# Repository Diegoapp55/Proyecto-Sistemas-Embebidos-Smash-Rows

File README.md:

# Proyecto-Sistemas-Embebidos
Repositorio para el proyecto de Sistemas Embebidos 2022-2: Smash Rows

En la wiki de este repositorio se encuentra la documentación al respecto del proyecto.

Integrantes: 
* Raúl Andrés Guzmán Mayorga
* Sergio Andrés Guevara Contreras
* Diego Alejandro Sánchez Mendoza
* Eduardo Toro Bernal

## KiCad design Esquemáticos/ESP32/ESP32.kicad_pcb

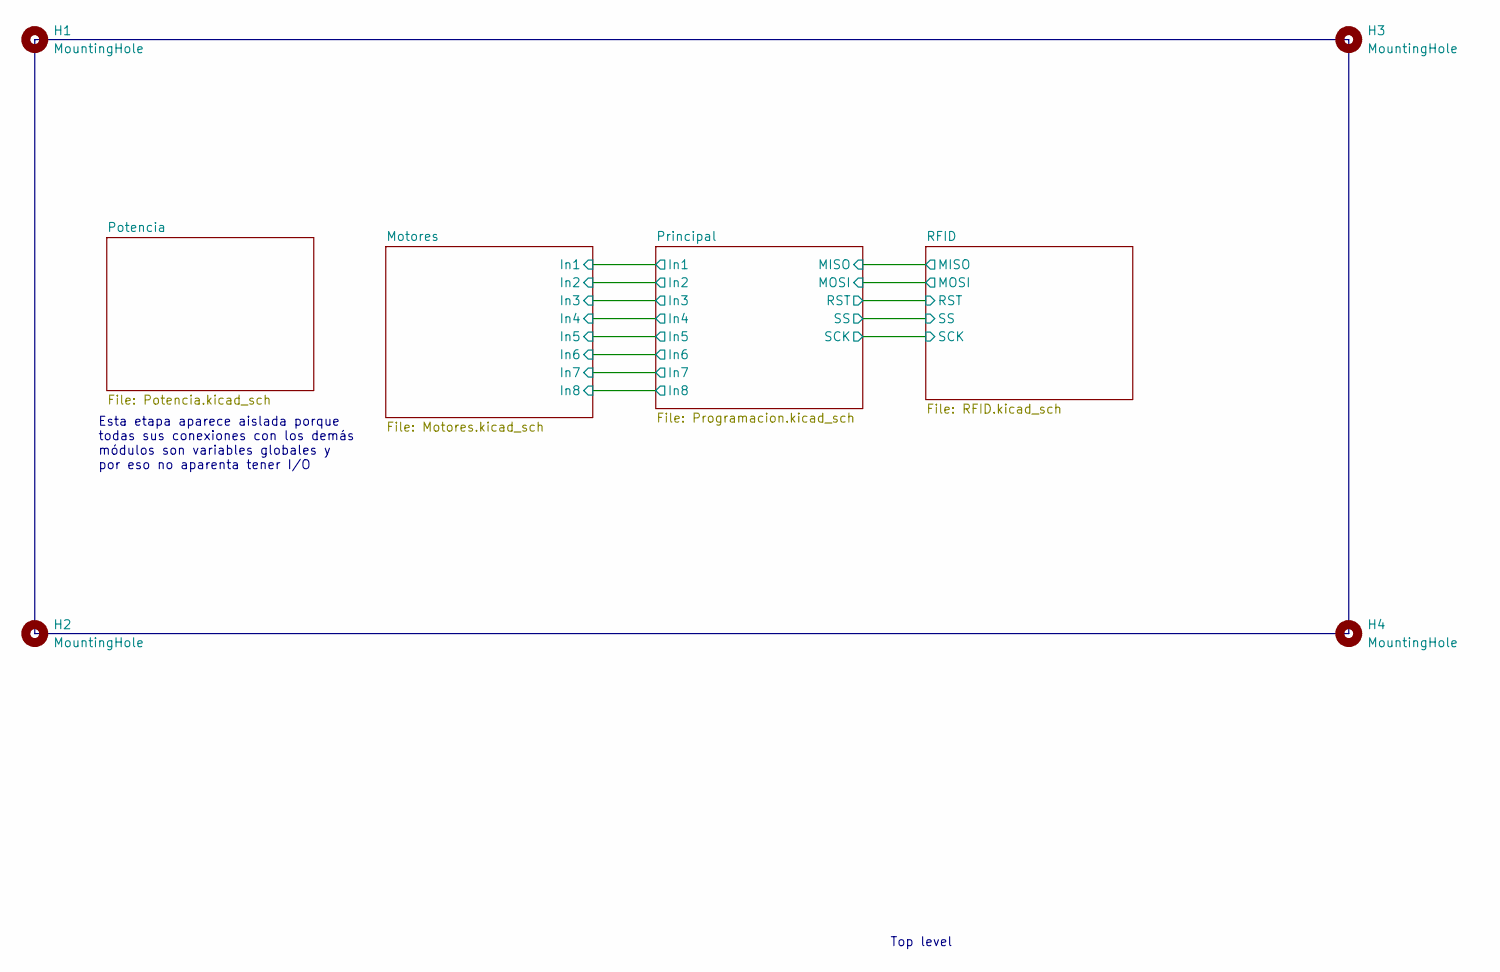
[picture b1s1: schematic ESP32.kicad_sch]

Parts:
H1, H2, H3, H4: MountingHole; MountingHole_2.5mm

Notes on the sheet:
Esta etapa aparece aislada porque todas sus conexiones con los demás módulos son variables globales y por eso no aparenta tener I/O
Top level

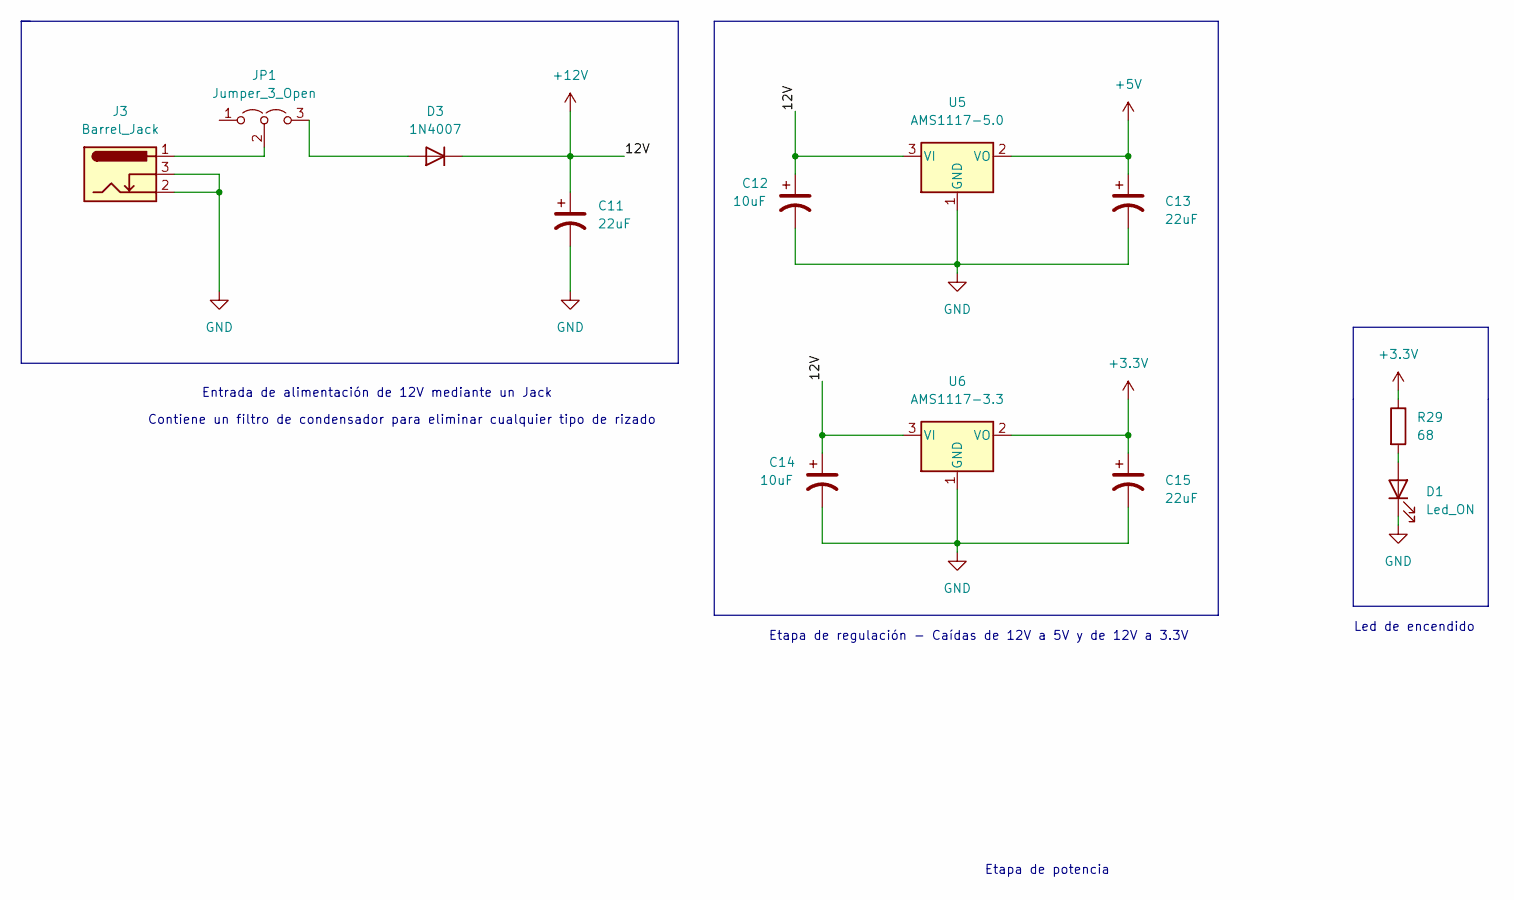
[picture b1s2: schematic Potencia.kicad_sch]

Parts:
C11, C13, C15: 22uF; C_0805_2012Metric_Pad1.18x1.45mm_HandSolder
C12, C14: 10uF; C_0805_2012Metric_Pad1.18x1.45mm_HandSolder
D1: Led_ON; LED_0603_1608Metric_Pad1.05x0.95mm_HandSolder
D3: 1N4007; D_SMA_Handsoldering
J3: Barrel_Jack; BarrelJack_GCT_DCJ200-10-A_Horizontal
JP1: Jumper_3_Open; PinHeader_1x03_P2.54mm_Vertical
R29: 68; R_1206_3216Metric_Pad1.30x1.75mm_HandSolder
U5: AMS1117-5.0; SOT-223-3_TabPin2
U6: AMS1117-3.3; SOT-223-3_TabPin2

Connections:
+3.3V: C15.1, R29.1, U6.2 (VO); also elsewhere on the board
+12V: C11.1, C12.1, C14.1, D3.1 (K), U5.3 (VI), U6.3 (VI)
GND: C11.2, C12.2, C13.2, C14.2, C15.2, D1.1 (K), J3.2, J3.3, U5.1 (GND), U6.1 (GND); also elsewhere on the board
unnamed: D1.2 (A), R29.2
unnamed: D3.2 (A), JP1.3 (B)
unnamed: J3.1, JP1.2 (C)

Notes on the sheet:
Entrada de alimentación de 12V mediante un Jack
Led de encendido
Contiene un filtro de condensador para eliminar cualquier tipo de rizado
Etapa de regulación - Caídas de 12V a 5V y de 12V a 3.3V
Etapa de potencia

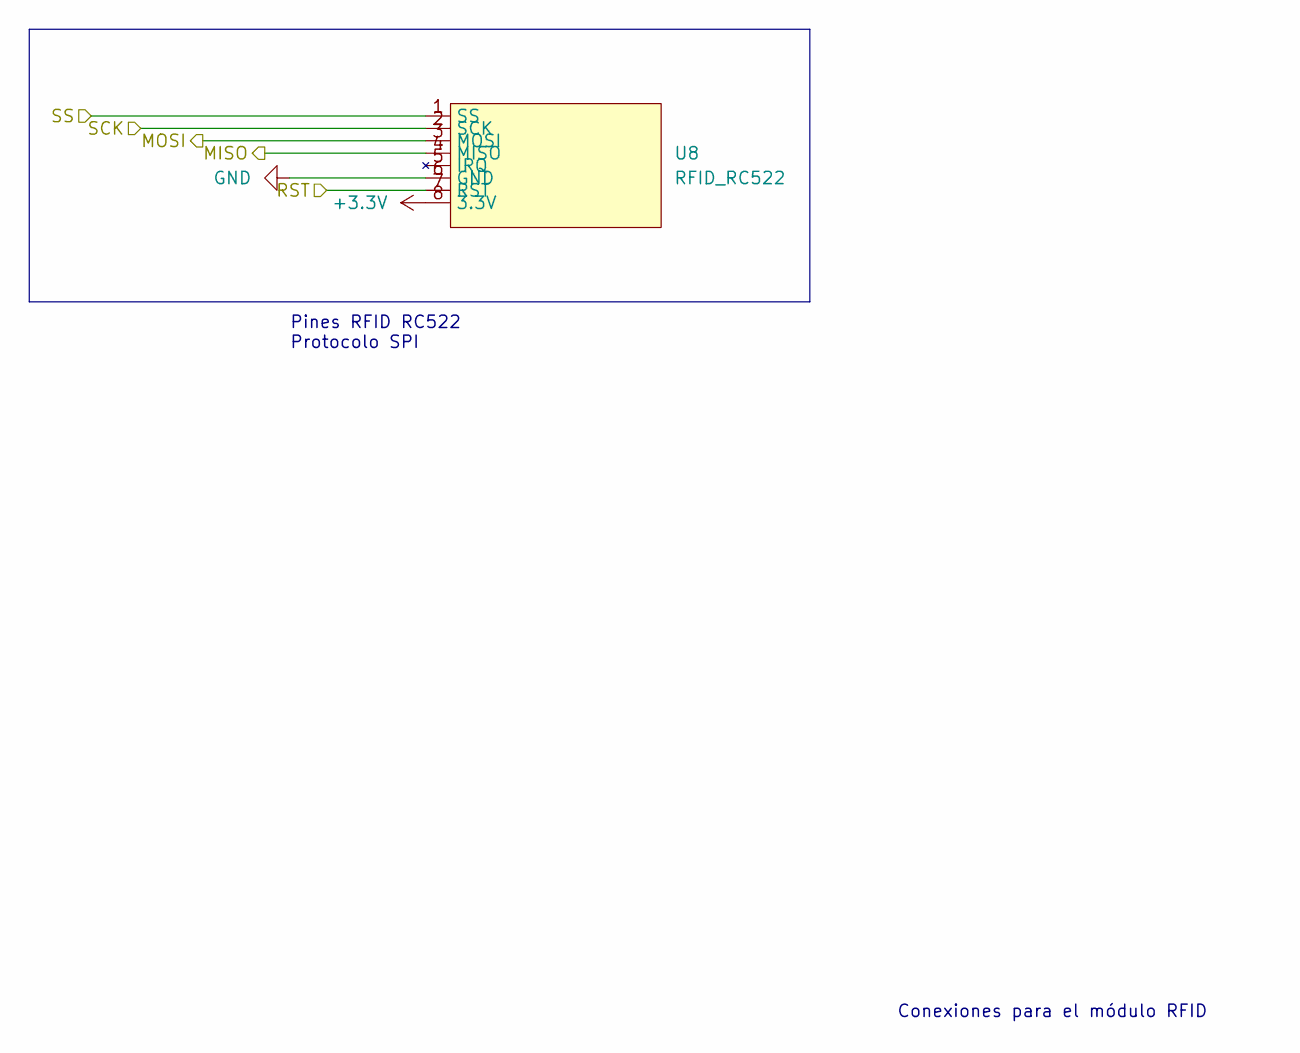
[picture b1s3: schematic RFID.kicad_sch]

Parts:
U8: RFID_RC522; JST_EH_B8B-EH-A_1x08_P2.50mm_Vertical

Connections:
+3.3V: U8.8 (3.3V); also elsewhere on the board
/Principal/MISO: U8.4 (MISO); also elsewhere on the board
/Principal/MOSI: U8.3 (MOSI); also elsewhere on the board
/Principal/RST: U8.7 (RST); also elsewhere on the board
/Principal/SCK: U8.2 (SCK); also elsewhere on the board
/Principal/SS: U8.1 (SS); also elsewhere on the board
GND: U8.6 (GND); also elsewhere on the board

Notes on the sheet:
Conexiones para el módulo RFID
Pines RFID RC522 Protocolo SPI

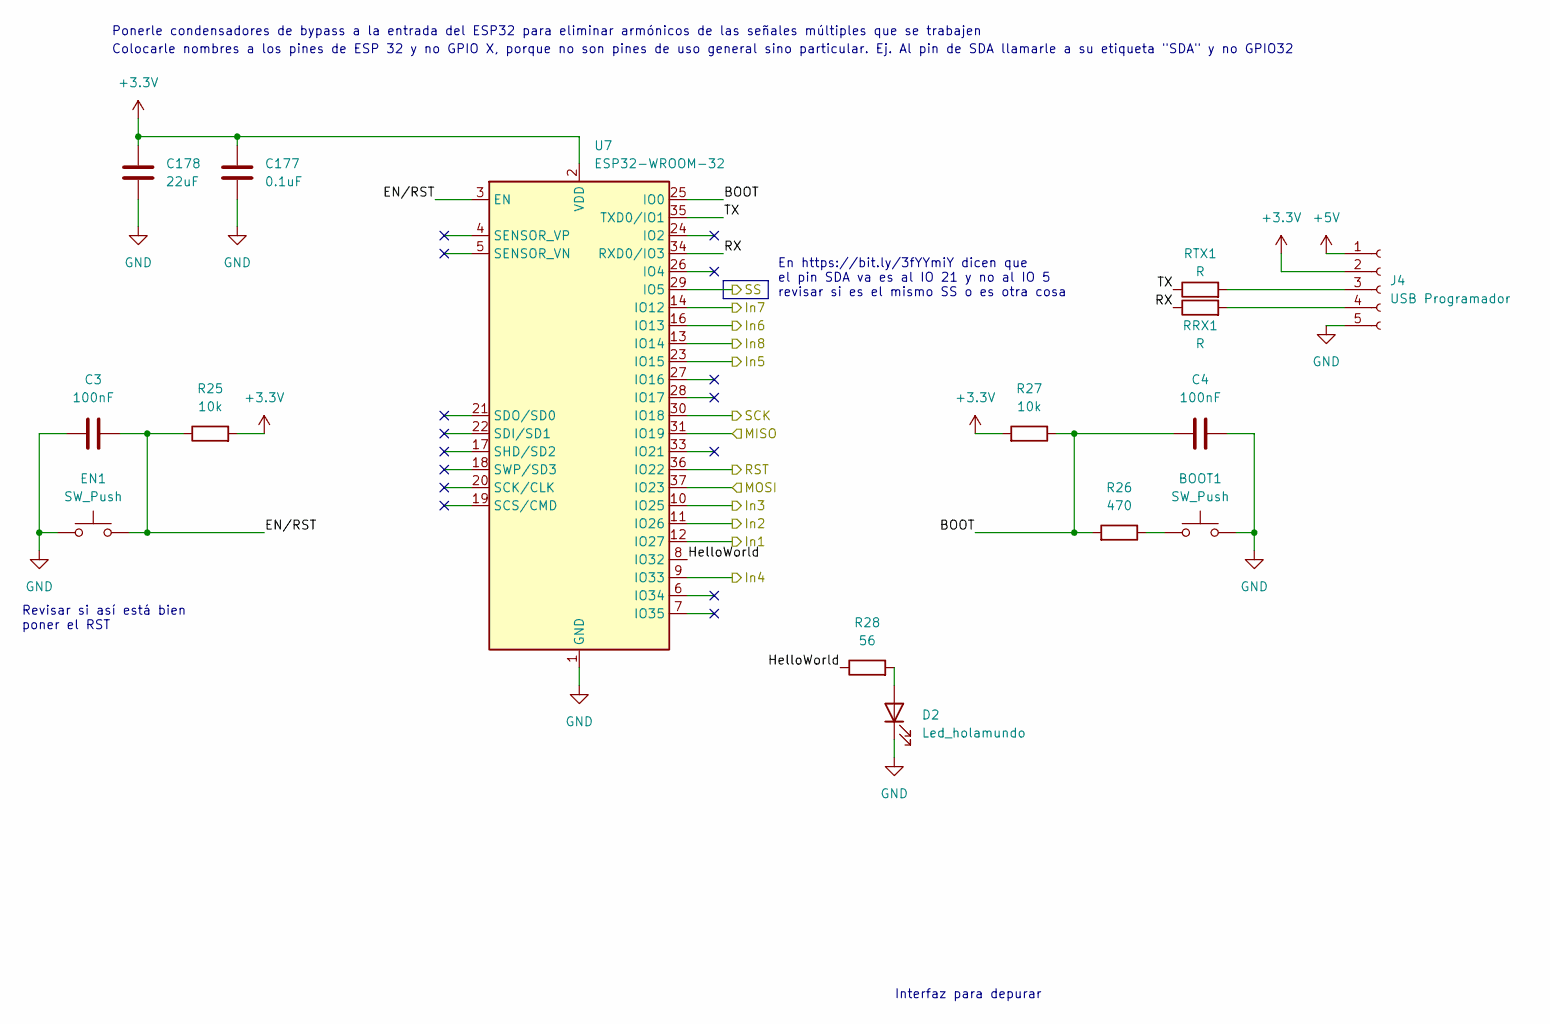
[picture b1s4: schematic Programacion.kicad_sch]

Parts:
BOOT1: SW_Push; SW_SPST_TL3305A
C3, C4: 100nF; C_0603_1608Metric_Pad1.08x0.95mm_HandSolder
C177: 0.1uF; C_0603_1608Metric_Pad1.08x0.95mm_HandSolder
C178: 22uF; C_0603_1608Metric_Pad1.08x0.95mm_HandSolder
D2: Led_holamundo; LED_0603_1608Metric_Pad1.05x0.95mm_HandSolder
EN1: SW_Push; SW_SPST_TL3305A
J4: USB Programador; PinHeader_1x05_P2.54mm_Vertical
R25, R27: 10k; R_0603_1608Metric_Pad0.98x0.95mm_HandSolder
R26: 470; R_0603_1608Metric_Pad0.98x0.95mm_HandSolder
R28: 56; R_0603_1608Metric_Pad0.98x0.95mm_HandSolder
RRX1: R; R_0603_1608Metric_Pad0.98x0.95mm_HandSolder
RTX1: R; R_0603_1608Metric_Pad0.98x0.95mm_HandSolder
U7: ESP32-WROOM-32

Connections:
+3.3V: C177.1, C178.1, J4.2, R25.2, R27.2, U7.2 (VDD); also elsewhere on the board
/Motores/In1: U7.12 (IO27); also elsewhere on the board
/Motores/In2: U7.11 (IO26); also elsewhere on the board
/Motores/In3: U7.10 (IO25); also elsewhere on the board
/Motores/In4: U7.9 (IO33); also elsewhere on the board
/Motores/In5: U7.23 (IO15); also elsewhere on the board
/Motores/In6: U7.16 (IO13); also elsewhere on the board
/Motores/In7: U7.14 (IO12); also elsewhere on the board
/Motores/In8: U7.13 (IO14); also elsewhere on the board
/Principal/BOOT: C4.2, R26.2, R27.1, U7.25 (IO0)
/Principal/EN/RST: C3.2, EN1.2, R25.1, U7.3 (EN)
/Principal/HelloWorld: R28.1, U7.8 (IO32)
/Principal/MISO: U7.31 (IO19); also elsewhere on the board
/Principal/MOSI: U7.37 (IO23); also elsewhere on the board
/Principal/RST: U7.36 (IO22); also elsewhere on the board
/Principal/RX: J4.4, RRX1.1, RRX1.2, U7.34 (RXD0/IO3)
/Principal/SCK: U7.30 (IO18); also elsewhere on the board
/Principal/SS: U7.29 (IO5); also elsewhere on the board
/Principal/TX: J4.3, RTX1.1, RTX1.2, U7.35 (TXD0/IO1)
GND: BOOT1.1, C3.1, C4.1, C177.2, C178.2, D2.1 (K), EN1.1, J4.5, U7.1 (GND), U7.15 (GND), U7.38 (GND), U7.39 (GND); also elsewhere on the board
unnamed: BOOT1.2, R26.1
unnamed: D2.2 (A), R28.2

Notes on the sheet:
En https://bit.ly/3fYYmiY dicen que el pin SDA va es al IO 21 y no al IO 5 revisar si es el mismo SS o es otra cosa
Ponerle condensadores de bypass a la entrada del ESP32 para eliminar armónicos de las señales múltiples que se trabajen
Revisar si así está bien poner el RST
Colocarle nombres a los pines de ESP 32 y no GPIO X, porque no son pines de uso general sino particular. Ej. Al pin de SDA llamarle a su etiqueta "SDA" y no GPIO32
Interfaz para depurar

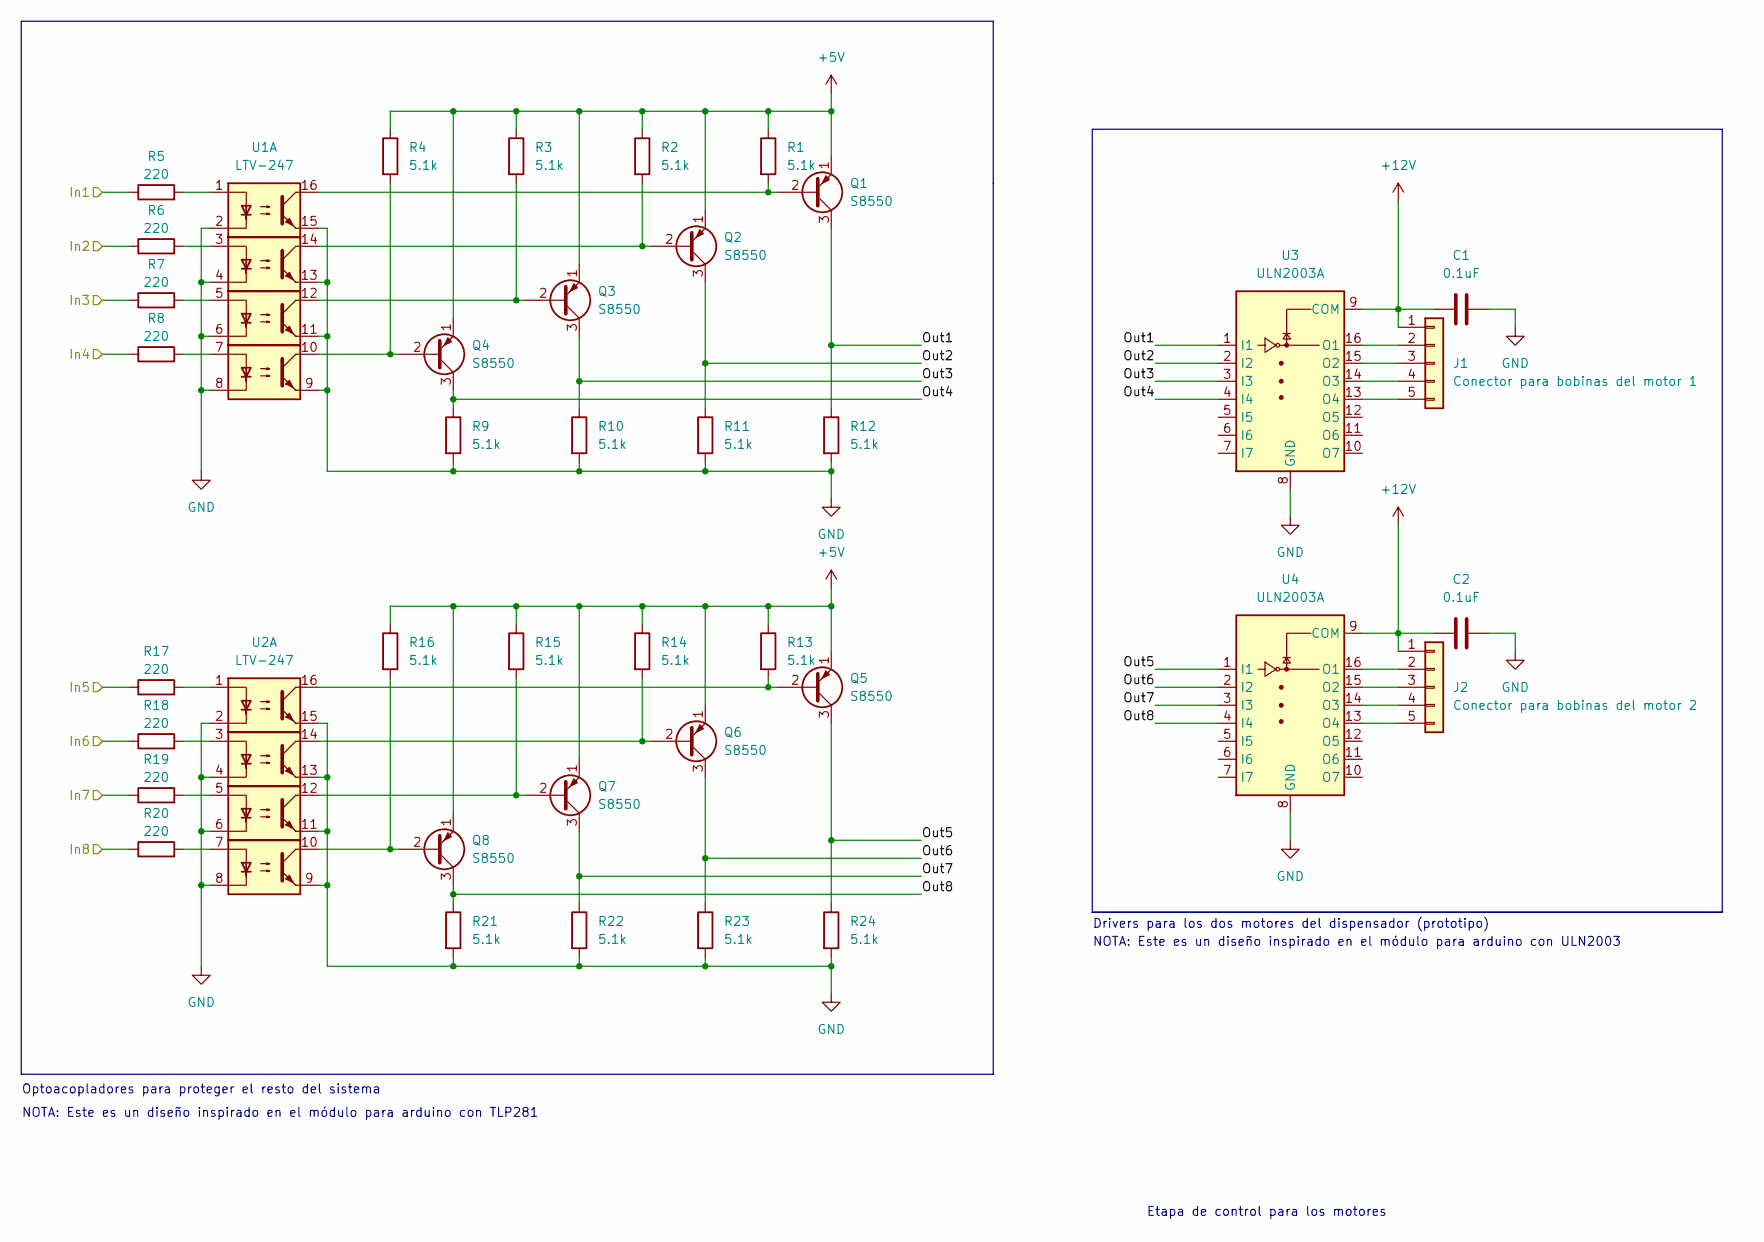
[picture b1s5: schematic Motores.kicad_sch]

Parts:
C1, C2: 0.1uF; C_0805_2012Metric_Pad1.18x1.45mm_HandSolder
J1: Conector para bobinas del motor 1; JST_EH_B5B-EH-A_1x05_P2.50mm_Vertical
J2: Conector para bobinas del motor 2; JST_EH_B5B-EH-A_1x05_P2.50mm_Vertical
Q1, Q2, Q3, Q4, Q5, Q6, Q7, Q8: S8550; TSOT-23
R1, R2, R3, R4, R9, R10, R11, R12, R13, R14, R15, R16, R21, R22, R23, R24: 5.1k; R_0805_2012Metric_Pad1.20x1.40mm_HandSolder
R5, R6, R7, R8, R17, R18, R19, R20: 220; R_0805_2012Metric_Pad1.20x1.40mm_HandSolder
U1, U2: LTV-247; DIP-16_W7.62mm_Socket
U3, U4: ULN2003A; DIP-16_W7.62mm_Socket

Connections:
/Motores/In1: R5.1; also elsewhere on the board
/Motores/In2: R6.1; also elsewhere on the board
/Motores/In3: R7.1; also elsewhere on the board
/Motores/In4: R8.1; also elsewhere on the board
/Motores/In5: R17.1; also elsewhere on the board
/Motores/In6: R18.1; also elsewhere on the board
/Motores/In7: R19.1; also elsewhere on the board
/Motores/In8: R20.1; also elsewhere on the board
/Motores/Out1: Q1.3 (C), R12.1, U3.1 (I1)
/Motores/Out2: Q2.3 (C), R11.1, U3.2 (I2)
/Motores/Out3: Q3.3 (C), R10.1, U3.3 (I3)
/Motores/Out4: Q4.3 (C), R9.1, U3.4 (I4)
/Motores/Out5: Q5.3 (C), R24.1, U4.1 (I1)
/Motores/Out6: Q6.3 (C), R23.1, U4.2 (I2)
/Motores/Out7: Q7.3 (C), R22.1, U4.3 (I3)
/Motores/Out8: Q8.3 (C), R21.1, U4.4 (I4)
GND: C1.2, C2.2, R9.2, R10.2, R11.2, R12.2, R21.2, R22.2, R23.2, R24.2, U1.2, U1.4, U1.6, U1.8, U1.9, U1.11, U1.13, U1.15, U2.2, U2.4, U2.6, U2.8, U2.9, U2.11, U2.13, U2.15, U3.8 (GND), U4.8 (GND); also elsewhere on the board
unnamed: J1.2, U3.16 (O1)
unnamed: J1.3, U3.15 (O2)
unnamed: J1.4, U3.14 (O3)
unnamed: J1.5, U3.13 (O4)
unnamed: J2.2, U4.16 (O1)
unnamed: J2.3, U4.15 (O2)
unnamed: J2.4, U4.14 (O3)
unnamed: J2.5, U4.13 (O4)
unnamed: Q1.2 (B), R1.2, U1.16
unnamed: Q2.2 (B), R2.2, U1.14
unnamed: Q3.2 (B), R3.2, U1.12
unnamed: Q4.2 (B), R4.2, U1.10
unnamed: Q5.2 (B), R13.2, U2.16
unnamed: Q6.2 (B), R14.2, U2.14
unnamed: Q7.2 (B), R15.2, U2.12
unnamed: Q8.2 (B), R16.2, U2.10
unnamed: R5.2, U1.1
unnamed: R6.2, U1.3
unnamed: R7.2, U1.5
unnamed: R8.2, U1.7
unnamed: R17.2, U2.1
unnamed: R18.2, U2.3
unnamed: R19.2, U2.5
unnamed: R20.2, U2.7

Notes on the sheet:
Optoacopladores para proteger el resto del sistema
Drivers para los dos motores del dispensador (prototipo)
NOTA: Este es un diseño inspirado en el módulo para arduino con ULN2003
NOTA: Este es un diseño inspirado en el módulo para arduino con TLP281
Etapa de control para los motores

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
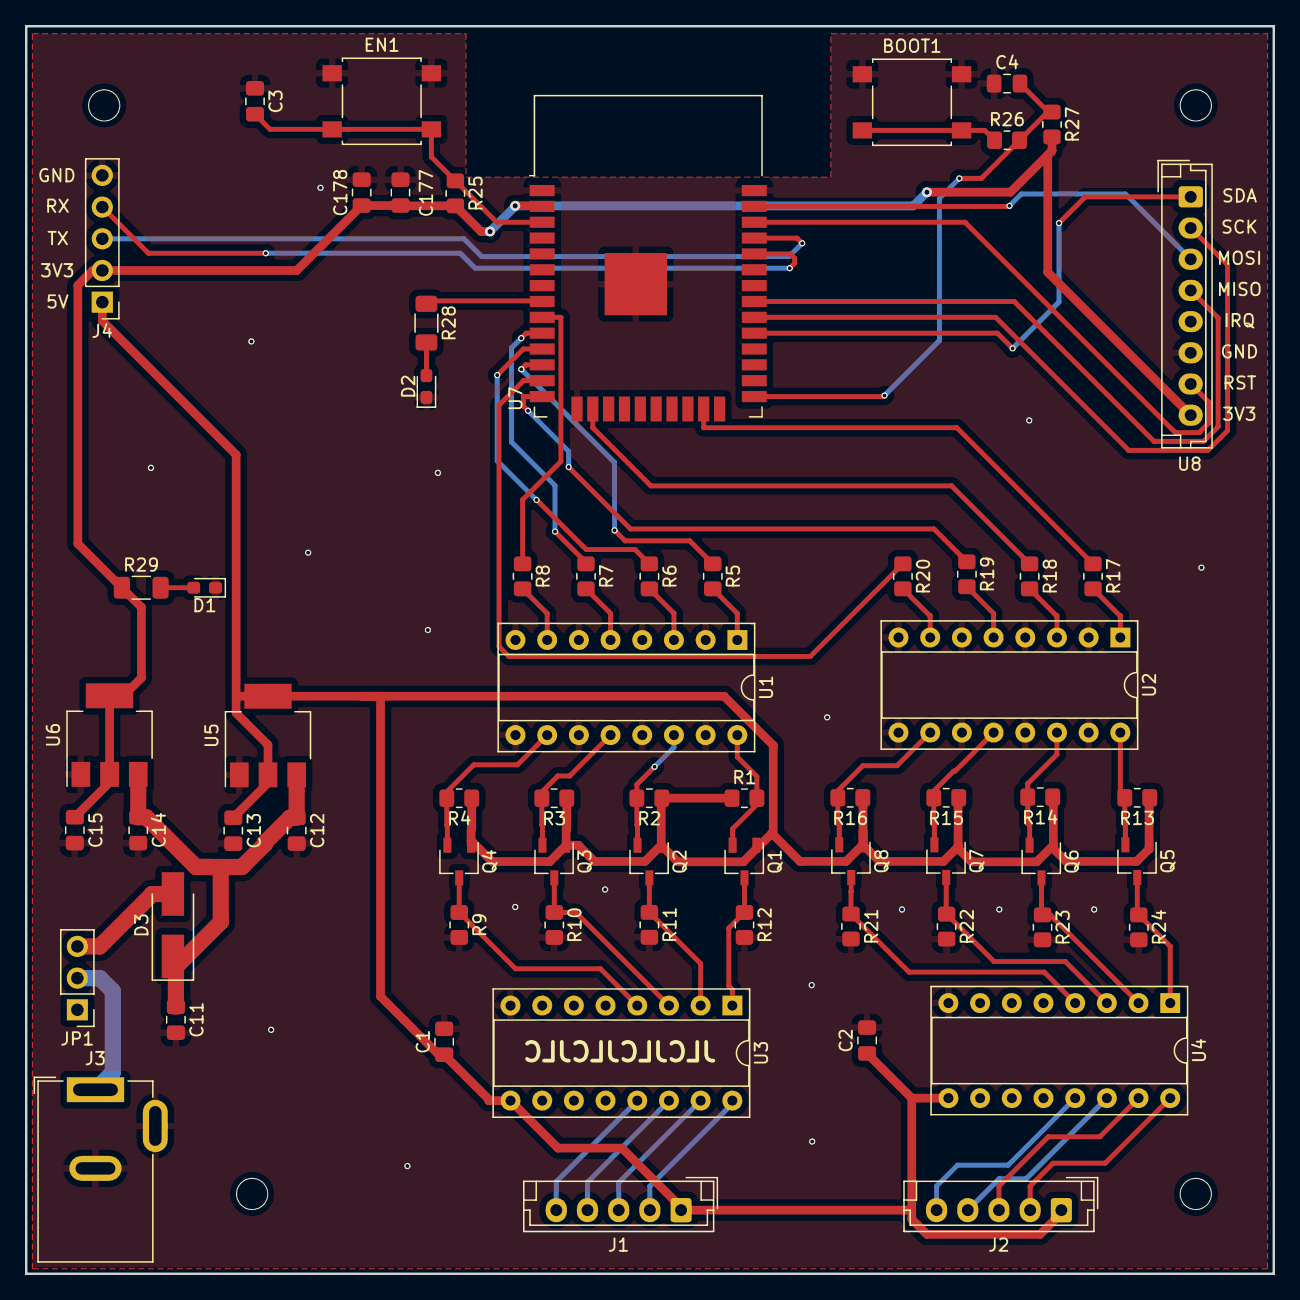
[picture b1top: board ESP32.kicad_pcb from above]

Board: 2 copper layers, 100.0 x 100.0 mm, 70 parts (0 on the bottom side), 59 nets.

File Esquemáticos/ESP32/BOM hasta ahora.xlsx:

Column1 | Column2 | Column3
Source:
Date: | 16/10/2022 4:27:32 p. m.
Tool: | Eeschema (6.0.7)
Generator:
Component Count: | 72
Ref | Qnty | Value
BOOT1, | 1 | pulsador
C1, C2, C3, C4, C177, | 5 | 0.1uF
C11, C13, C15, C178, | 4 | 22uF
C12, C14, | 2 | 10uF
D1, | 1 | led
D2, | 1 | led
D3, | 1 | 1n4007
EN1, | 1 | pulsador
H1, H2, H3, H4, | 4 | NA
J1, | 1 | JST 1x5
J2, | 1 | JST 1x5
J3, | 1 | jack 12V
J4, | 1 | pin header hembra 1x5
Q1, Q2, Q3, Q4, Q5, Q6, Q7, Q8, | 8 | pnp s8550 o equiv
R1, R2, R3, R4, R9, R10, R11, R12, R13, R14, R15, R16, R21, R22, R23, R24, | 16 | 5.1kΩ
R5, R6, R7, R8, R17, R18, R19, R20, | 8 | 220Ω
R25, R27, | 2 | 10kΩ
R26, | 1 | 470Ω
R28, R29, | 2 | 56Ω
RRX1, | 1 | pend
RTX1, | 1 | pend
SW1, | 1 | dip switch x1
U1, U2, | 2 | ltv247 o equiv
U3, U4, | 2 | uln2003
U5, | 1 | ams1117-5V
U6, | 1 | ams1117-3V3
U7, | 1 | esp32wroom
U8, | 1 | rfid_rc522

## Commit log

2022-08-22 Create Imagens
2022-08-23 Cambie el nombre de la carpeta para imagenes
2022-08-23 Diagrama de flujo subido para la wiki
2022-08-23 Imagenes modificadas
2022-09-08 New Diagram Blocks ESP32
2022-09-08 New ESP32
2022-09-13 Potencia
2022-09-13 Esquemáticos para control de motores añadidos
2022-09-13 Agregada la parte de motores a la jerarquía de esquemáticos
    :+1:
2022-09-13 Comentario sobre el zener de potencia
    Comentario agregado sobre el diodo utilizado en la etapa de potencia
2022-09-14 mensaje
2022-09-14 Añadido Modo Programación
2022-09-14 Correcciones De Banderas
2022-09-15 Cambios hechos al esquemático, faltan detalles
    Revisar el discord para dejar todo al día con el feedback de hoy
2022-09-21 Actualizada la etapa de motores
2022-09-21 Actualización Potencia
    21/09/2022
2022-09-21 actualización raul
2022-09-21 Intentando ponerle footprints a los motores
2022-09-21 No hay cambios lol
    Lolazo
2022-09-22 Arreglando los bugs xd
2022-09-22 Cajas Potencia
    lolololol
2022-09-22 actualización raul_2
2022-09-23 actualizacion raul 3.0
2022-09-24 gente creo q borre cosas sin querer :(
2022-09-29 Mas commits :sunglasses:
    Agragados números de los componentes
2022-09-29 Push mid :V
2022-09-29 Voy mid
2022-09-29 auxilio
2022-09-29 Support
2022-10-04 Algunas huellas añadidas
2022-10-04 Potencia Cap
    xd?
2022-10-04 me falta el led de programacion
2022-10-04 Asignación Huellas de Resistencias
2022-10-04 Actualización Capacitores
2022-10-04 Eliminando el error de autosave
2022-10-04 Etiquetas globales para alimentación añadidas
2022-10-04 añadí leds
2022-10-06 Potencia - Final
2022-10-09 Actualizadas las huellas de R y C
    De acuerdo con la recomendación del profe, ahora todas son 0603.
2022-10-10 ruteo
2022-10-10 ruteo2
2022-10-10 Clases de pistas agregadas
2022-10-10 wey noooooooooo (no guardé xd)
2022-10-10 PCB versión 1 (Faltan zonas de GND)
2022-10-11 Ruteo y zonas de cobre. Modo_serio.jpg
2022-10-11 Muchos cambios a la PCB
    Moví varios elementos para poder añadir los agujeros de montaje y agregué esos agujeros de montaje.
    También moví el pulsador de BOOT para que quede estéticamente mejor a ambos lados del módulo ESP32 WROOM
    Importante:
    Nos faltan todas las conexiones de los optoacopladores con la ESP 32 xD (urgente revisar cuales pines sirven para eso).
2022-10-12 Añadí las conexiones con los optoacopladores
    Además arreglé la posición de algunas vías.
2022-10-13 PCB terminada (pendiente de aprobación)
    :sunglasses: :sunglasses: :sunglasses:
2022-10-13 Actualizada la PCB con impresiones de qué es cada pin de los conectores
    Pendiente: Agregar capacitor de bypass en la entrada de 3v3 del ESP32 y listo, a comerciar con los chinos
2022-10-14 Placa con Logo
2022-10-16 Auxilio? Bypass 3.3V ESP32
2022-10-17 Huellas actualizadas según los vendedores locales
    Falta la del optoacoplador y actualizar la placa. Además, dependiendo de la resñpuesta del profe tocaría re-diseñar todo :c
2022-10-18 NewPCB
2022-10-18 PCB terminada
    Revisar los gerber y los drill :3
2022-10-20 PCB lista uwu
2022-10-20 Numero de Orden añadido
2022-10-21 Hello Everyone from App
2022-10-27 imagenes_wiki
2022-10-30 Agregué un comentario en uno de los archivos
    Ppara probar si nos deja hacer commits pull push y eso normalito
2022-10-31 Agregados los archivos de zephyrexample para empezar a trabajar firmware
2022-11-01 Main Interface
2022-11-01 Button customization
2022-11-03 archivos ayuda johnny
2022-11-03 Change Button Color
2022-11-03 Revert "archivos ayuda johnny"
    This reverts commit 669989e4da2792f3f5c896bb74d22718ca704e6b.
2022-11-03 Organization First Layout
2022-11-03 archivos ayuda johnny2
2022-11-03 Revert "archivos ayuda johnny2"
    This reverts commit 164cdeed01ab3e5182ba8d0ec19adf24cddcc623.
2022-11-03 archivos ayuda johnny3
2022-11-03 Functional Button Exit App
2022-11-04 Interface settings
2022-11-04 Added app logo
2022-11-08 Rivales? Pilas con los cambios
2022-11-08 Ejemplo de Prueba
2022-11-10 editamos overlay de blink e hicimos motores paso a paso
2022-11-10 Actualización motoreslol
2022-11-10 archivo original de motores paso a paso
2022-11-15 InsertDocument Layout
2022-11-15 Button functionality: Back and Insert Document
2022-11-15 Main Button: Scanner Document
2022-11-15 Button Back Scanner
2022-11-15 Button Back About Us
2022-11-15 TeamWork
2022-11-15 TeamWork: Images
2022-11-15 Definition Pin Motors
2022-11-15 Update Motors
2022-11-15 Motors Update
2022-11-15 Definicion de Salidas
    Siuuuu
2022-11-17 Definition Motors
2022-11-17 Estamos sin desayunito :C
2022-11-18 Changes of App
2022-11-18 New Logo
2022-11-18 Button "Config" and final logo
2022-11-18 New Button: Config
2022-11-18 Codigo motores actualizado, no sirve ni el blinky :(
    Para que el profe nos ayude a encontrar el error en el código por fa. Gracias
2022-11-18 Buttons Data Base
2022-11-19 Buttons Instance of DB
2022-11-19 Config Buttons DB Actions
2022-11-19 fix stepper example
2022-11-19 Users are saved in the DB
2022-11-19 Borrando carpetas redundantes
    antes de hacer merge con la ayuda del profe
2022-11-20 Actualicé gitignore
    Para que no muestre como que se hicieron cambios en el repo cada que abrimos kicad para solo revisar algo y git piensa que cambiamos archivos
2022-11-20 Había creado mal la línea de gitignore
    (No es para obtener más commits que Raul, lo juro :v)
2022-11-20 Parece que así si sirve el gitignore
2022-11-20 Cambios de acuerdo con las sugerencias del profe
2022-11-20 Pruebas 19-11
    Modificación del blink para que prenda 2 leds (Ese si funcionó, pero descubrí que al asignar el pin 27 para que haga GPIO_TOOGLE)
    Modifiqué también el de motores para lograr que funcione el blink de depuración con la ayuda del profe. Ahora toca ver si al escribir info en los pines del motor 1 (que ya inicializan sin problema), 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
2022-11-22 motores paso a paso funcional
2022-11-24 Actualizados los ejemplos de zephyr
2022-11-24 DB Drugs
2022-11-24 WIFI_HD-CR7
2022-11-24 Buttons DB Drugs
2022-11-24 Logos o le'go :v
2022-11-24 codigo 2 motores v2
2022-11-29 Añadí el código de arduino para revisar
    Lee los UID de las tarjetas que se acerquen al módulo RFID
2022-12-03 Button Save Drugs Ok
2022-12-03 Button Search Users
2022-12-03 Logo para el RFID agregado
2022-12-04 arduino q envia 1s?
2022-12-04 arduino conectado a eso q envia 1s?
2022-12-04 Cajotaxd dwg
2022-12-05 Agregadas señales de depuración para comunicación entre arduino y esp32
2022-12-05 Agregado el UID del carnet de Diego para pruebas RFID
2022-12-05 arduino conectado a eso q envia 1s?v3
2022-12-05 RFID, esp y arduino :)
2022-12-05 Caja Actualizada
2022-12-05 PDF Caja
2022-12-05 Actualizado el código de Arduino
    Ya sirve RFID así uwu
2022-12-06 Change DB Users
2022-12-06 Bugs fix
2022-12-06 Scanner Doc Active
2022-12-06 About Us Configuration
2022-12-06 Implementation App
2022-12-06 nuevas imagenes
2022-12-06 nuevas imagenesv2
2022-12-06 socket_wifi
2022-12-07 Search Document User
2022-12-07 Canceled claim
2022-12-07 Button Claim Done
2022-12-07 Pre-Final App
2022-12-07 App Finalizada Con Foto De Diego
2022-12-07 Image Doc
2022-12-07 supongo que.. se acabó
2022-12-07 Salto de fé
2022-12-07 Nuevas imágenes
2022-12-07 imagenes nuevas
2022-12-07 ADSAFasf
2022-12-07 Remontando, amén
2022-12-08 último push
2022-12-12 Final Commit
